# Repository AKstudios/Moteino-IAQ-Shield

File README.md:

# Moteino IAQ Shield

This is an indoor air quality shield for Motenio that measures temperature, humidity, light intensity, PM2.5, CO2 and VOC concentrations. Power through micro USB.
<br><br>
Sensors used:<br>
SHT31/35<br>
TSL2591<br>
CCS811<br>
PMS5003/7003 (molex connector for external module)<br>

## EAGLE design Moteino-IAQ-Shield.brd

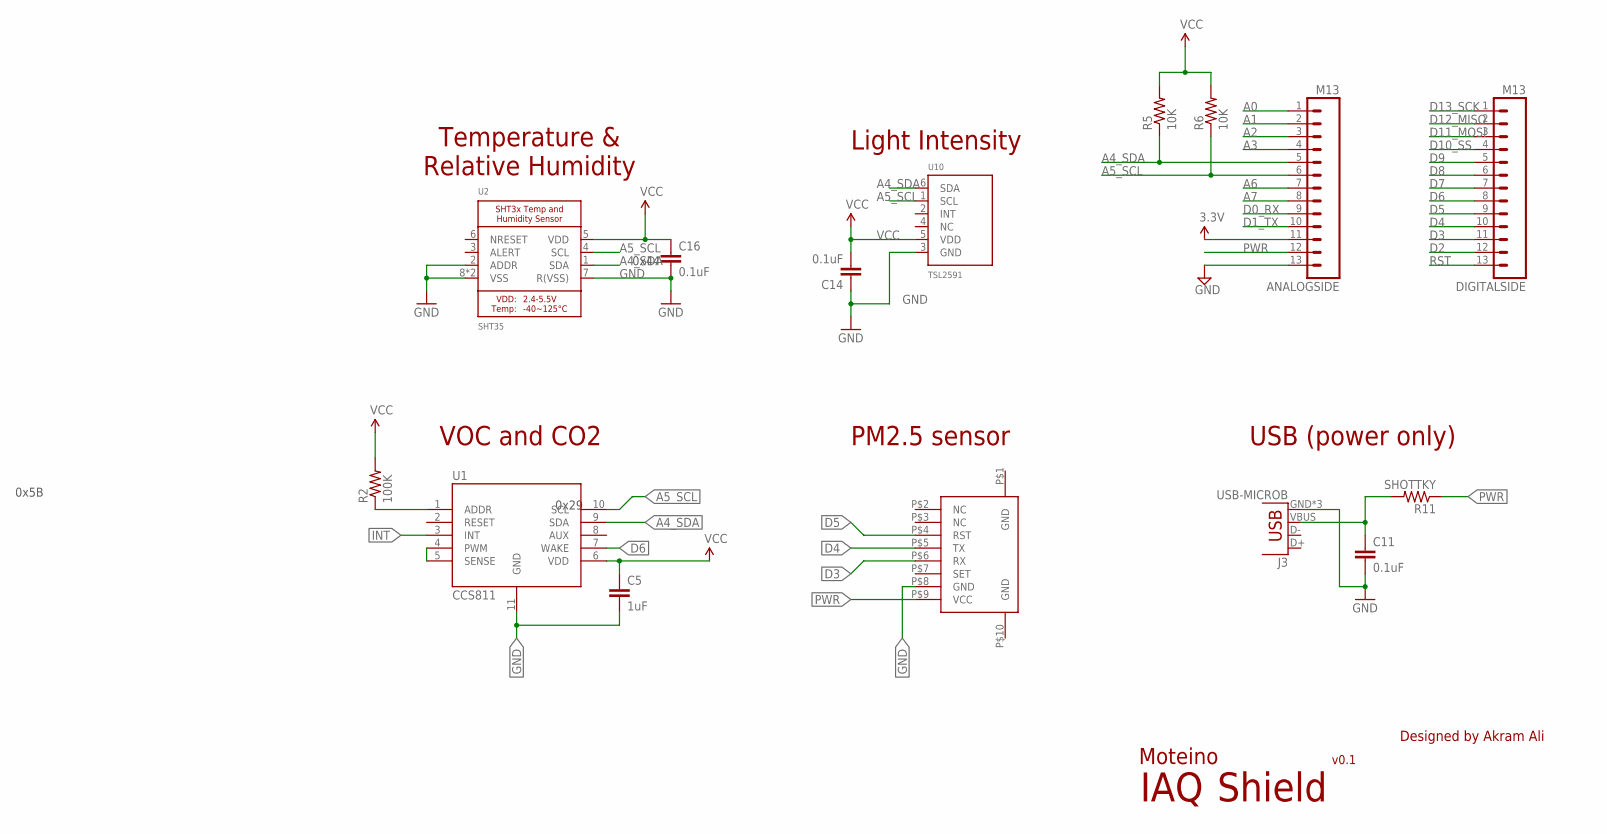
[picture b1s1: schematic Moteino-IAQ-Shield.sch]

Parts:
ANALOGSIDE: M13; 1X13
C5: 1uF; 0805; MPN CC0805KKX7R7BB105
C11, C14, C16: 0.1uF; 0805; MPN CC0805KRX7R9BB104
DIGITALSIDE: M13; 1X13
J3: USB-MICROB; MPN 47346-0001
R2: 100K; 0805; MPN 311-100KCRCT-ND
R5, R6: 10K; 0805; MPN RC0805FR-0710KL
R11: SHOTTKY; 0805; MPN SD0805S040S0R5
U1: CCS811; LGA; MPN CCS811
U2: SHT35; SHT3X; MPN SHT35-DIS-B
U10: TSL2591; DFN6_TAOS; MPN TSL25911FN
U$1: PMS5003/7003; 0532610871

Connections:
A0: ANALOGSIDE.1
A1: ANALOGSIDE.2
A2: ANALOGSIDE.3
A3: ANALOGSIDE.4
A4_SDA: ANALOGSIDE.5, R5.1, U1.9 (SDA), U2.1 (SDA), U10.6 (SDA)
A5_SCL: ANALOGSIDE.6, R6.1, U1.10 (SCL), U2.4 (SCL), U10.1 (SCL)
A6: ANALOGSIDE.7
A7: ANALOGSIDE.8
D0_RX: ANALOGSIDE.9
D1_TX: ANALOGSIDE.10
D2: DIGITALSIDE.12
D3: DIGITALSIDE.11, U$1.P$6 (RX)
D4: DIGITALSIDE.10, U$1.P$5 (TX)
D5: DIGITALSIDE.9, U$1.P$4 (RST)
D6: DIGITALSIDE.8, U1.7 (WAKE)
D7: DIGITALSIDE.7
D8: DIGITALSIDE.6
D9: DIGITALSIDE.5
D10_SS: DIGITALSIDE.4
D11_MOSI: DIGITALSIDE.3
D12_MISO: DIGITALSIDE.2
D13_SCK: DIGITALSIDE.1
GND: ANALOGSIDE.13, C5.2, C11.2, C14.1, C16.2, J3.GND, J3.MT1 (GND), J3.MT2 (GND), U1.11 (GND), U2.2 (ADDR), U2.7 (R(VSS)), U2.8 (VSS), U2.THERMAL (VSS), U10.3 (GND), U$1.P$8 (GND)
INT: U1.3 (INT)
unnamed: R2.1, U1.1 (ADDR)
unnamed: U1.4 (PWM), U1.5 (SENSE)
PWR: ANALOGSIDE.12, R11.1, U$1.P$9 (VCC)
RST: DIGITALSIDE.13
VBUS: C11.1, J3.VBUS, R11.2
VCC: ANALOGSIDE.11, C5.1, C14.2, C16.1, R2.2, R5.2, R6.2, U1.6 (VDD), U2.5 (VDD), U10.5 (VDD)

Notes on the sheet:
Moteino
Designed by Akram Ali
IAQ
Temperature & Relative Humidity
0x44
Light Intensity
0x29
PM2.5 sensor
USB (power only)
Shield
v0.1
VOC and CO2
0x5B

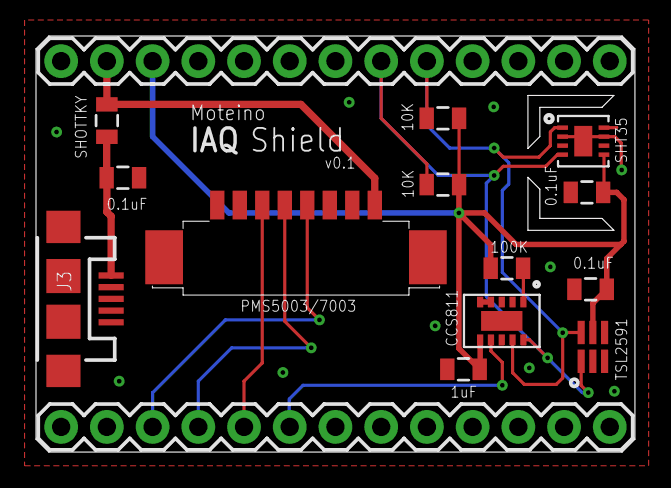
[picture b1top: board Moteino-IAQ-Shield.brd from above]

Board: 2 copper layers, 33.2 x 23.1 mm, 15 parts (0 on the bottom side), 12 nets.

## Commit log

2017-04-12 :confetti_ball: Added .gitattributes & .gitignore files
2017-04-12 Added EAGLE files
2017-04-13 Trace and component adjustments
2017-04-13 Added OSH Park render
2017-04-17 Updated library for Molex connector
2017-05-08 Connected GND trace for SHT sensor

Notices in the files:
parts and their libraries:
SparkFun-Connectors: Licensing: CC v3.0 Share-Alike You are welcome to use this library for commercial purposes.
SparkFun-Passives: Licensing: Creative Commons ShareAlike 4.0 International - https://creativecommons.org/licenses/by-sa/4.0
